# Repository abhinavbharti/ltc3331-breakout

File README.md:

## Open, low-cost experimentation board for the LTC3331 energy harvesting chip
	
This project contains design- and production-files for a
low-cost LTC3331 energy harvesting development-, breakout- and test-board.

It's specifically designed to be inexpensive, yet open and comprehensive:
* Full design files for KiCad EDA
* 10cm x 10cm PCB with 2 layers
* Full pin breakout
* Less-comprehensive headers for pins usually required
* LIR2032 holder and alternative battery port
* All default options can be jumpered on or off
* Supercap pads provided

(Above: v0.1, image rendered by KiCad EDA)

(Above: v0.1, actual photo of both sides)

## Releases and History

All production files for releases can be found in the
production/ directory. All required production files for
PCB production should be zipped in a way that allows immediate upload
to your preferred online PCB manufacturer.

v0.1 is the first version of the PCB. It has a few minor issues
(see Errata), but is fine for testing.

## Errata

### v0.1

v0.1 works fine, but there are a few issues that should be
addressed for another release:

Schematic:

* jumper for BBIN-BATIN connection is not needed.

* scatter more GND connectors for oscilloscope use

* maybe provide circuit for higher current charging,
  as seen in datasheet figure 7, pg 27?

* extra small header for GND/AC1/AC2/VIN

Footprints:

* footprints for 22uF inductors on bottom layer are way too large.
  a Taiyo-Yuden NR-30xx handsoldering footprint would be fine and should
  be moved to the front side. then there would be no components on the bottom.

* replace all capacitance footprints >= 10uF with larger
  footprint for e.g. tantalum capacitor.

* make cap footprints dual-use: through-hole AND smd?

PCB Placement / Routing:

* reorder all selection jumpers so they comply the the datasheet table

Silkscreen:

* mark down input voltage limits (3-19V)

* add white box for charge-current-resistor value placed by user

* if enough place, print cap values (and voltage ratings?)

Other:

* pdf schematic was missing in release files (was added later).
  next release should contain that immediately.

## Prior Art and Alternatives

Please note: personally I did not obtain any of the following
alternatives, so any comparison is a rough guess.

DC2151A is the de-facto standard demo- and dev-board that
Linear Technology created for this chip.
However, it's really expensive. (200+ €/$)

The "LTC3331 Energy Harvester, DC Converter and Charger"
by Blue Spark Labs is a much cheaper alternative to the
official dev-board.
But it seemingly does not offer comprehensive access to all pins
and full breakout options. Also, worldwide shipping can be
quite expensive, it seems.

## Use

When you want to use or modify the design in KiCad, you should get used
to handling git-submodules. I keep my custom footprints and symbols in
a separate repository so I can re-use them.

Have fun!

## Feedback

If you have design improvements, find it useful or stupid, or
want to let me know anything else, just let me know ;).

## License, copyright

The design is released under the OSHW 1.0 license as defined
by [https://www.oshwa.org/definition/].

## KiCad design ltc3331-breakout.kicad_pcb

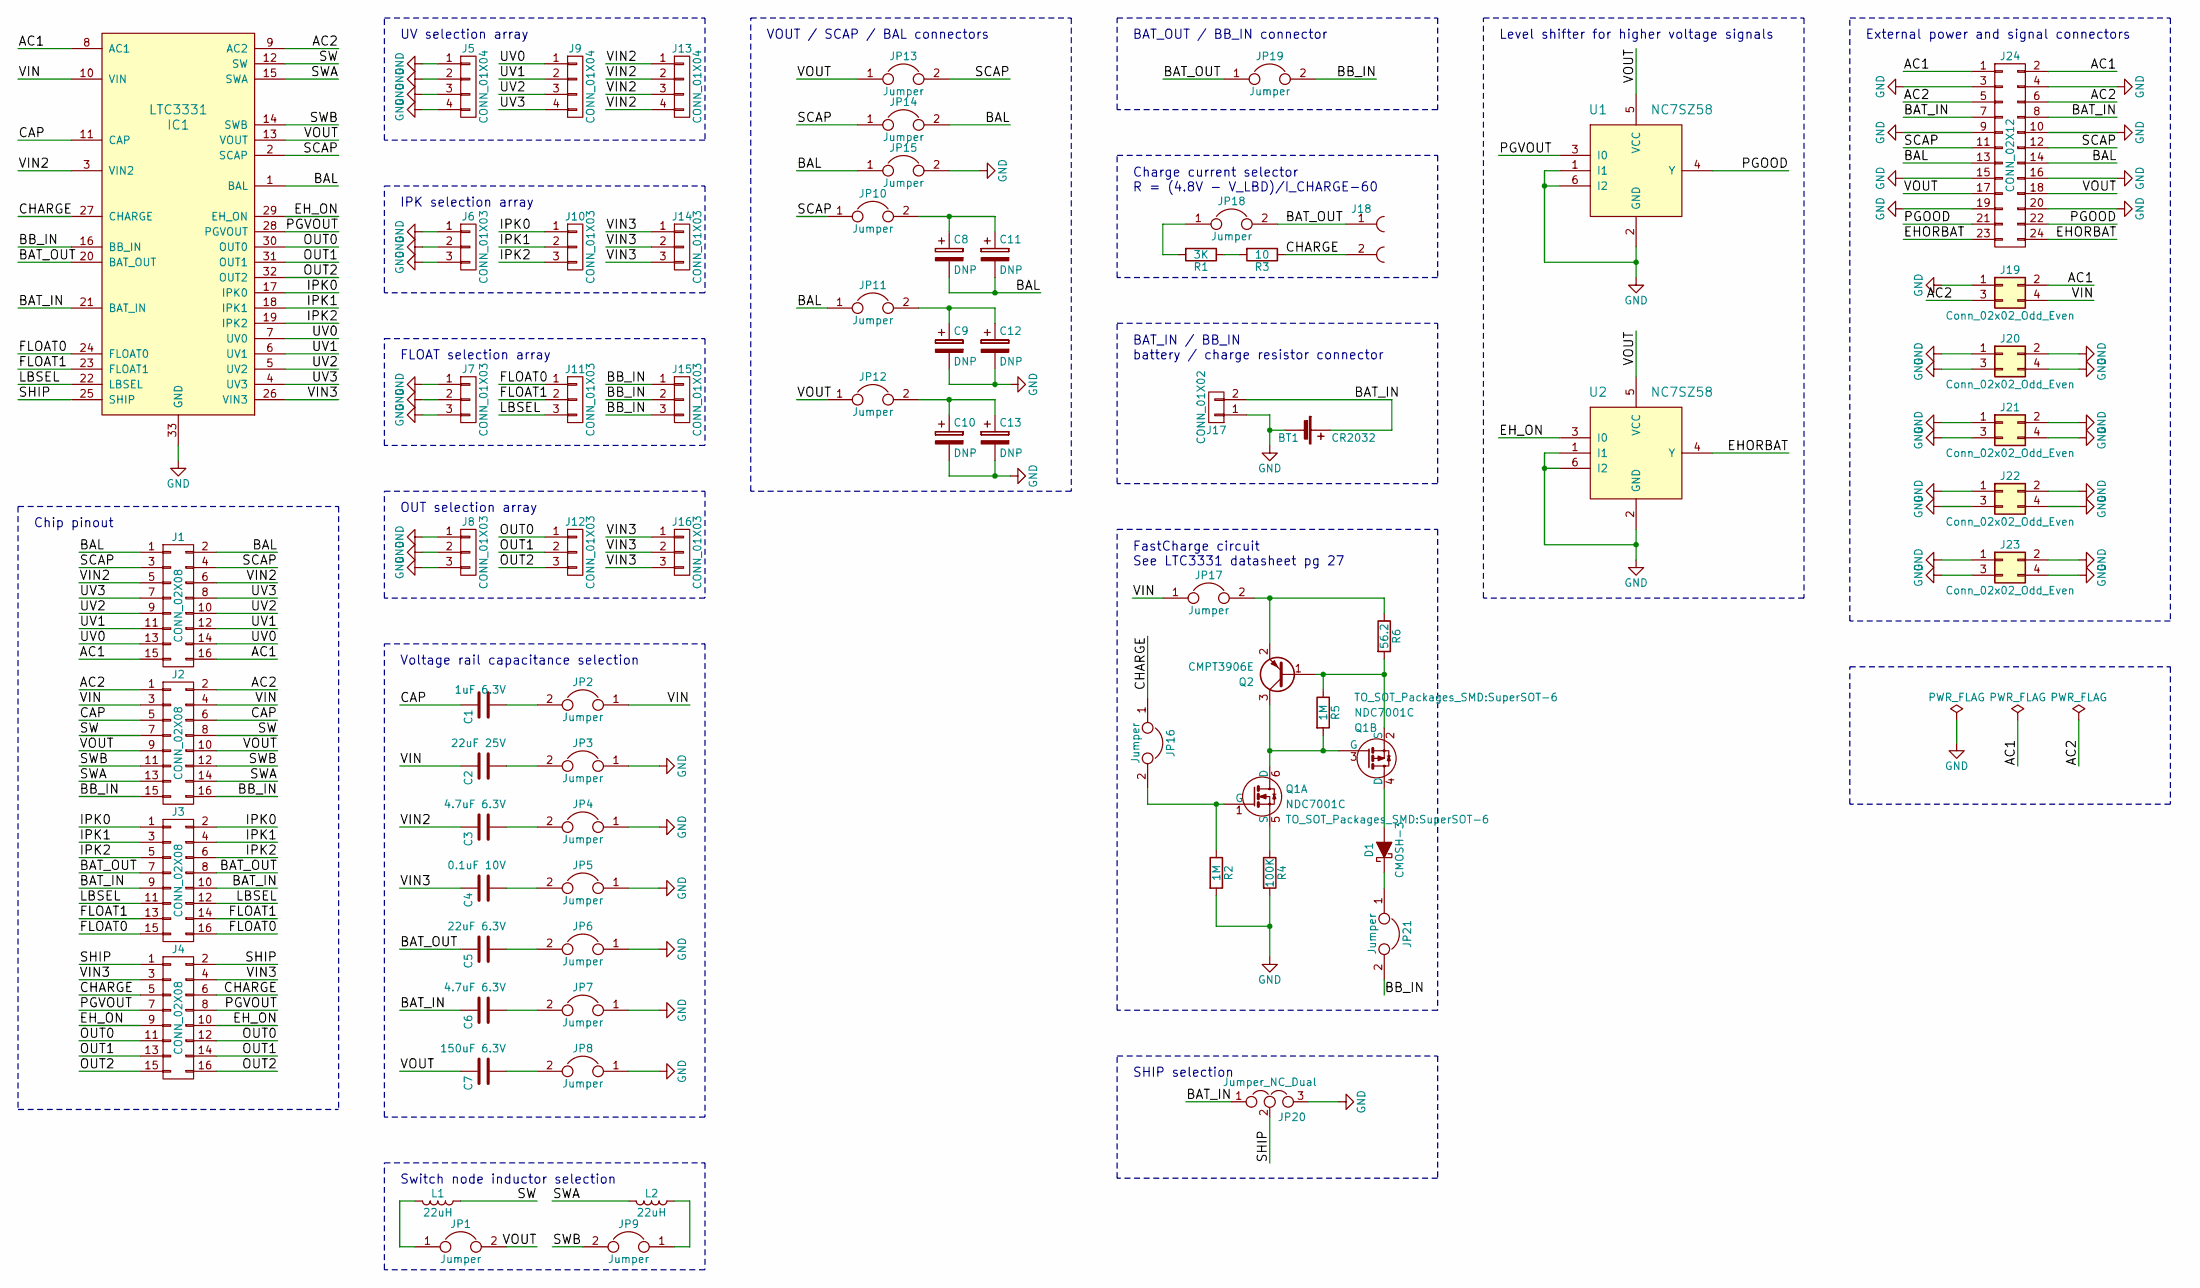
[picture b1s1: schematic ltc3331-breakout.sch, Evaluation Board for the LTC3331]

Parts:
BT1: CR2032; SMTU-2032-LF; Farnell 1216354
C1: 1uF 6.3V; C_1206_HandSoldering
C2: 22uF 25V; CAP_Generic_SMD_Radial_D10.0mm_P2.50mm_P5.00mm
C3, C6: 4.7uF 6.3V; CAP_Generic_SMD_Radial_D10.0mm_P2.50mm_P5.00mm
C4: 0.1uF 10V; C_1206_HandSoldering
C5: 22uF 6.3V; CAP_Generic_SMD_Radial_D10.0mm_P2.50mm_P5.00mm
C7: 150uF 6.3V; CAP_Generic_SMD_Radial_D10.0mm_P2.50mm_P5.00mm
C8, C9, C10, C11, C12, C13: DNP; CP_Elec_10x10
D1: CMOSH-3; D_SOD-523
IC1: LTC3331; QFN-32-1EP_5x5mm_Pitch0.5mm
J1, J2, J3, J4: CONN_02X08; Pin_Header_Straight_2x08_Pitch2.54mm
J5, J9, J13: CONN_01X04; Pin_Header_Straight_1x04_Pitch2.54mm
J6, J7, J8, J10, J11, J12, J14, J15, J16: CONN_01X03; Pin_Header_Straight_1x03_Pitch2.54mm
J17: CONN_01X02; Pin_Header_Straight_1x02_Pitch2.54mm
J18: CONN_01X02_FEMALE; Pin_Header_Straight_1x02_Pitch2.54mm
J19, J20, J21, J22, J23: Conn_02x02_Odd_Even; Pin_Header_Straight_2x02_Pitch2.54mm
J24: CONN_02X12; Pin_Header_Straight_2x12_Pitch2.54mm
JP1, JP2, JP3, JP4, JP5, JP6, JP7, JP8, JP9, JP10, JP11, JP12, JP13, JP14, JP15, JP16, JP17, JP18, JP19, JP21: Jumper; Pin_Header_Straight_1x02_Pitch2.54mm
JP20: Jumper_NC_Dual; Pin_Header_Straight_1x03_Pitch2.54mm
L1, L2: 22uH; Inductor_Taiyo-Yuden_NR-30xx_HandSoldering
Q1: NDC7001C; SuperSOT-6
Q2: CMPT3906E; SOT-23
R1: 3K; R_1206_HandSoldering
R2, R5: 1M; R_1206_HandSoldering
R3: 10; R_1206_HandSoldering
R4: 100K; R_1206_HandSoldering
R6: 56.2; R_1206_HandSoldering
U1, U2: NC7SZ58; SOT-363_SC-70-6_Handsoldering

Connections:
/AC1: IC1.8 (AC1), J1.15, J1.16, J19.2, J24.1, J24.2
/AC2: IC1.9 (AC2), J2.1, J2.2, J19.3, J24.5, J24.6
/BAL: C8.2, C11.2, IC1.1 (BAL), J1.1, J1.2, J24.13, J24.14, JP11.1, JP14.2, JP15.1
/BAT_IN: BT1.1 (+), C6.1, IC1.21 (BAT_IN), J3.9, J3.10, J17.2, J24.7, J24.8, JP20.1
/BAT_OUT: C5.1, IC1.20 (BAT_OUT), J3.7, J3.8, J18.1, JP18.2, JP19.1
/BB_IN: IC1.16 (BB_IN), J2.15, J2.16, J15.1, J15.2, J15.3, JP19.2, JP21.2
/CAP: C1.1, IC1.11 (CAP), J2.5, J2.6
/CHARGE: IC1.27 (CHARGE), J4.5, J4.6, J18.2, JP16.1, R3.1
/EHORBAT: J24.23, J24.24, U2.4 (Y)
/EH_ON: IC1.29 (EH_ON), J4.9, J4.10, U2.3 (I0)
/FLOAT0: IC1.24 (FLOAT0), J3.15, J3.16, J11.1
/FLOAT1: IC1.23 (FLOAT1), J3.13, J3.14, J11.2
/IPK0: IC1.17 (IPK0), J3.1, J3.2, J10.1
/IPK1: IC1.18 (IPK1), J3.3, J3.4, J10.2
/IPK2: IC1.19 (IPK2), J3.5, J3.6, J10.3
/LBSEL: IC1.22 (LBSEL), J3.11, J3.12, J11.3
/OUT0: IC1.30 (OUT0), J4.11, J4.12, J12.1
/OUT1: IC1.31 (OUT1), J4.13, J4.14, J12.2
/OUT2: IC1.32 (OUT2), J4.15, J4.16, J12.3
/PGOOD: J24.21, J24.22, U1.4 (Y)
/PGVOUT: IC1.28 (PGVOUT), J4.7, J4.8, U1.3 (I0)
/SCAP: IC1.2 (SCAP), J1.3, J1.4, J24.11, J24.12, JP10.1, JP13.2, JP14.1
/SHIP: IC1.25 (SHIP), J4.1, J4.2, JP20.2
/SW: IC1.12 (SW), J2.7, J2.8, L1.1
/SWA: IC1.15 (SWA), J2.13, J2.14, L2.1
/SWB: IC1.14 (SWB), J2.11, J2.12, JP9.2
/UV0: IC1.7 (UV0), J1.13, J1.14, J9.1
/UV1: IC1.6 (UV1), J1.11, J1.12, J9.2
/UV2: IC1.5 (UV2), J1.9, J1.10, J9.3
/UV3: IC1.4 (UV3), J1.7, J1.8, J9.4
/VIN: C2.1, IC1.10 (VIN), J2.3, J2.4, J19.4, JP2.1, JP17.1
/VIN2: C3.1, IC1.3 (VIN2), J1.5, J1.6, J13.1, J13.2, J13.3, J13.4
/VIN3: C4.1, IC1.26 (VIN3), J4.3, J4.4, J14.1, J14.2, J14.3, J16.1, J16.2, J16.3
/VOUT: C7.1, IC1.13 (VOUT), J2.9, J2.10, J24.17, J24.18, JP1.2, JP12.1, JP13.1, U1.5 (VCC), U2.5 (VCC)
GND: BT1.2 (-), C9.2, C10.2, C12.2, C13.2, IC1.33 (GND), J5.1, J5.2, J5.3, J5.4, J6.1, J6.2, J6.3, J7.1, J7.2, J7.3, J8.1, J8.2, J8.3, J17.1, J19.1, J20.1, J20.2, J20.3, J20.4, J21.1, J21.2, J21.3, J21.4, J22.1, J22.2, J22.3, J22.4, J23.1, J23.2, J23.3, J23.4, J24.3, J24.4, J24.9, J24.10, J24.15, J24.16, J24.19, J24.20, JP3.1, JP4.1, JP5.1, JP6.1, JP7.1, JP8.1, JP15.2, JP20.3, R2.2, R4.2, U1.1 (I1), U1.2 (GND), U1.6 (I2), U2.1 (I1), U2.2 (GND), U2.6 (I2)
unnamed: C1.2, JP2.2
unnamed: C2.2, JP3.2
unnamed: C3.2, JP4.2
unnamed: C4.2, JP5.2
unnamed: C5.2, JP6.2
unnamed: C6.2, JP7.2
unnamed: C7.2, JP8.2
unnamed: C10.1, C13.1, JP12.2
unnamed: C8.1, C11.1, JP10.2
unnamed: C9.1, C12.1, JP11.2
unnamed: D1.1 (K), JP21.1
unnamed: D1.2 (A), Q1.4 (D)
unnamed: JP1.1, L1.2
unnamed: JP9.1, L2.2
unnamed: JP16.2, Q1.1 (G), R2.1
unnamed: JP17.2, Q2.2 (E), R6.1
unnamed: JP18.1, R1.2
unnamed: Q1.2 (S), Q2.1 (B), R5.1, R6.2
unnamed: Q1.3 (G), Q1.6 (D), Q2.3 (C), R5.2
unnamed: Q1.5 (S), R4.1
unnamed: R1.1, R3.2

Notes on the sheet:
OUT selection array
IPK selection array
UV selection array
FLOAT selection array
SHIP selection
Charge current selector R = (4.8V - V_LBD)/I_CHARGE-60
BAT_OUT / BB_IN connector
Switch node inductor selection
Chip pinout
Voltage rail capacitance selection
BAT_IN / BB_IN battery / charge resistor connector
VOUT / SCAP / BAL connectors
External power and signal connectors
Level shifter for higher voltage signals
FastCharge circuit See LTC3331 datasheet pg 27

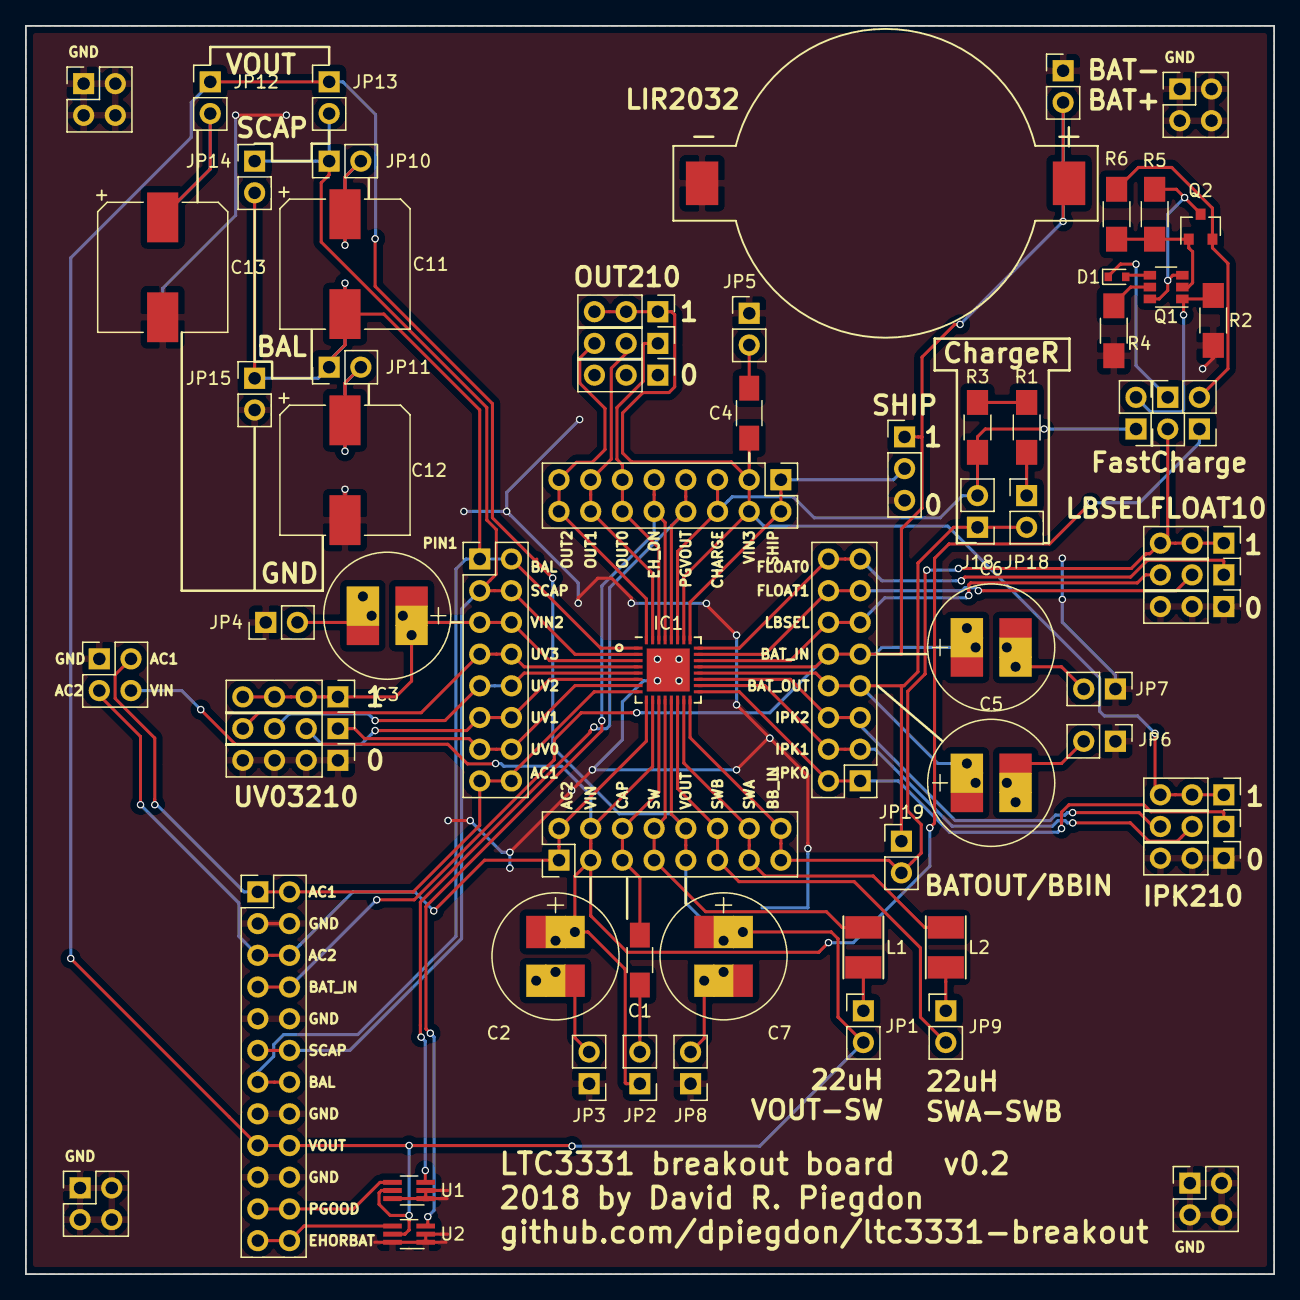
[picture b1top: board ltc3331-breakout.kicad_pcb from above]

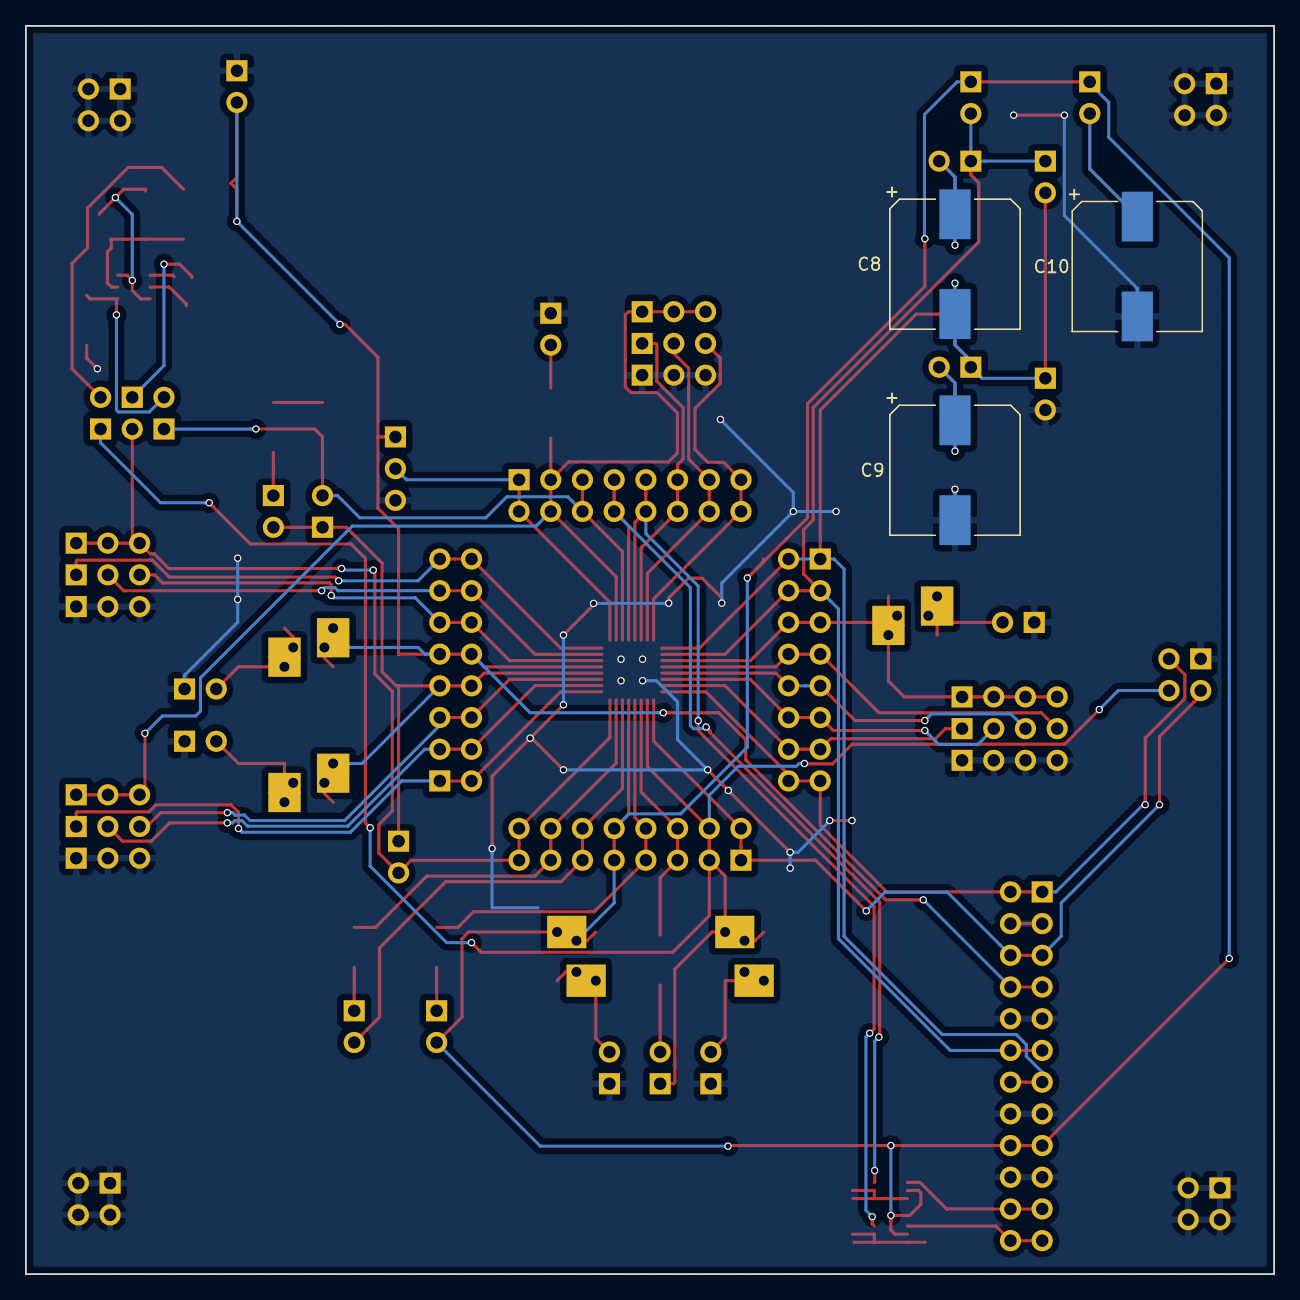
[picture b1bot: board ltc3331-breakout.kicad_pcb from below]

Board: 2 copper layers, 100.0 x 100.0 mm, 73 parts (3 on the bottom side), 56 nets.

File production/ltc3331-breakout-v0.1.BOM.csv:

"Id";"Designator";"Package";"Quantity";"Designation";"Supplier and ref";
1;"C7";"C_1206_HandSoldering";1;"150uF 6.3V";;;
2;"JP15";"Pin_Header_Straight_1x03_Pitch2.54mm";1;"Jumper_NC_Dual";;;
3;"FID**,FID**,FID**,FID**,FID**,FID**,FID**,FID**";"fiducial_i.5mm_o1.5mm";8;"fiducial_i.5mm_o1.5mm";;;
4;"REF**,REF**,REF**,REF**";"MountingHole_4.3mm_M4_Pad_Via";4;"MountingHole_4.3mm_M4_Pad_Via";;;
5;"C12,C8,C9,C10,C11,C13";"CP_Elec_10x10";6;"DNP";;;
6;"BT1";"SMTU-2032-LF";1;"CR2032";;;
7;"C1";"C_1206_HandSoldering";1;"1uF 6.3V";;;
8;"C2";"C_1206_HandSoldering";1;"22uF 25V";;;
9;"C3,C6";"C_1206_HandSoldering";2;"4.7uF 6.3V";;;
10;"C4";"C_1206_HandSoldering";1;"0.1uF 10V";;;
11;"C5";"C_1206_HandSoldering";1;"22uF 6.3V";;;
12;"IC1";"QFN-32-1EP_5x5mm_Pitch0.5mm";1;"LTC3331";;;
13;"J1,J6,J11";"Pin_Header_Straight_1x04_Pitch2.54mm";3;"CONN_01X04";;;
14;"J2,J3,J4,J7,J8,J9,J12,J13,J14";"Pin_Header_Straight_1x03_Pitch2.54mm";9;"CONN_01X03";;;
15;"J5";"Pin_Header_Straight_1x02_Pitch2.54mm";1;"CONN_01X02";;;
16;"J10";"Pin_Header_Straight_1x02_Pitch2.54mm";1;"CONN_01X02_FEMALE";;;
17;"J15";"Pin_Header_Straight_2x12_Pitch2.54mm";1;"CONN_02X12";;;
18;"J16,J17,J18,J19";"Pin_Header_Straight_2x08_Pitch2.54mm";4;"CONN_02X08";;;
19;"J20";"Pin_Header_Straight_2x04_Pitch2.54mm";1;"CONN_02X04";;;
20;"JP1,JP2,JP3,JP4,JP5,JP6,JP7,JP8,JP9,JP10,JP11,JP12,JP13,JP14,JP16,JP17,JP18,JP19";"Pin_Header_Straight_1x02_Pitch2.54mm";18;"Jumper";;;
21;"L1,L2";"Inductor_Wurth_HCI-1890";2;"22uH";;;
22;"R1";"R_1206_HandSoldering";1;"3K";;;
23;"R2";"R_1206_HandSoldering";1;"10";;;
24;"R3";"R_1206_HandSoldering";1;"100";;;
25;"U1,U2";"SOT-363_SC-70-6_Handsoldering";2;"NC7SZ58";;;
26;"REF***";"OSHW-Logo2_14.6x12mm_SilkScreen";1;"OSHW-Logo2_14.6x12mm_SilkScreen";;;
27;"REF**";"Symbol_KiCAD-Logo_CopperAndSilkScreenTop";1;"KiCAD Logo";;;

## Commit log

2017-07-04 initial, preliminary version
2017-07-04 initial setup with library
2017-07-04 schematic cleanup
2017-07-04 submodule license
2017-07-04 added level shifter for PGOOD, EHORBAT; cleanup; most footprints
2017-07-04 use lipo-connector instead of CR2477. cleanup.
2017-07-04 netlist
2017-07-05 basic routing and silk screen. verification pending.
2017-07-05 routing cleanup, copper pour cleanup, added mounting holes and more silk screen labels
2017-07-05 fixed silkscreen bug, layout cleanup, production stuff
2017-07-05 more cleanup
2017-07-05 finished v0.1 production files
2017-07-11 README and rendering of PCB
2017-09-03 updated status on v0.1
2017-09-06 replace 22uF inductor footprints with better ones
2017-09-06 move U1,U2 to front side to clear rear side of all required components.
2017-09-06 docs
2018-03-31 more fixmes for next revision
2018-03-31 more ideas for next revision
2018-05-12 readme cleanup
2018-05-12 schematic: applied some errata from v0.1
2018-05-12 routed changes
2018-05-12 added footprints
2018-05-12 replaced some capacitors with generic footprint, rerouted
